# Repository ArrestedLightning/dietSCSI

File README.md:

The dietSCSI is a SCSI disk emulator, designed to be low-cost while remaining highly functional.

Features
----------

* SMT-first design, optimized for modern low-cost assembly services
  * Target price of ~$10 each in small quantities from JLCPCB, fully assembled
  * This implies that the retail price for a fully-assembled board could be $20 with a 100% markup
* Can be [hand-assembled](https://youtu.be/Q2M2qIhKqx8) using only parts that are [readily available from DigiKey](https://www.digikey.com/short/dphdzd52) (Except for the STM32 microcontroller, but those aren't readily available anywhere at the moment)
* Integrated DB25 and 50-pin IDC connectors on one board.  A single PCB design covers multiple use cases, ideal for easy switching between multiple computers
  * This also means that you can use the dietSCSI itself as a DB-25 to 50-pin SCSI adapter in a pinch
* On-board termination (jumper-selectable)
* Design files for [3D printed cases](https://github.com/ArrestedLightning/dietSCSI/blob/main/Mechanical/README.md) are available in variants for both portable usage and 3.5" hard disk replacement
* 0.1" headers for external activity LEDs
* Can be powered via SCSI termination power or from an external source
* Designed to run firmware based on the open source [BlueSCSI firmware](https://github.com/erichelgeson/BlueSCSI/)
* [Default firmware](https://github.com/ArrestedLightning/dietSCSI_firmware/) has both [USB image passthrough](https://youtu.be/Y3mzckQU518) and [USB firmware update support](https://youtu.be/odwWRFDpAHM) built in (see the [usage page](https://github.com/ArrestedLightning/dietSCSI/blob/main/docs/usage.md) for details).

Documentation
--------
* [Ordering assembled boards from JLCPCB](https://github.com/ArrestedLightning/dietSCSI/blob/main/docs/ordering_boards.md)
* [Hand assembly](https://github.com/ArrestedLightning/dietSCSI/blob/main/docs/hand_assembly.md)
* [Finishing](https://github.com/ArrestedLightning/dietSCSI/blob/main/docs/finishing.md)
* [Usage](https://github.com/ArrestedLightning/dietSCSI/blob/main/docs/usage.md)
* [Test Results](https://github.com/ArrestedLightning/dietSCSI/blob/main/docs/testresults.md)

Acknowledgments
--------

* The [ARDSCSuino-stm32](https://github.com/ztto/ArdSCSino-stm32) project for the original implementation of STM32-to-SCSI hardware and firmware
* [This TI document](https://www.ti.com/lit/an/slla035/slla035.pdf) on SCSI termination
* The [BlueSCSI project](https://github.com/erichelgeson/BlueSCSI/) for their work on the firmware

BlueSCSI is a registered trademark.  This project is not affiliated with or endorsed by the BlueSCSI project.  Please do not contact the BlueSCSI people for support; use GitHub discussions or email me directly.

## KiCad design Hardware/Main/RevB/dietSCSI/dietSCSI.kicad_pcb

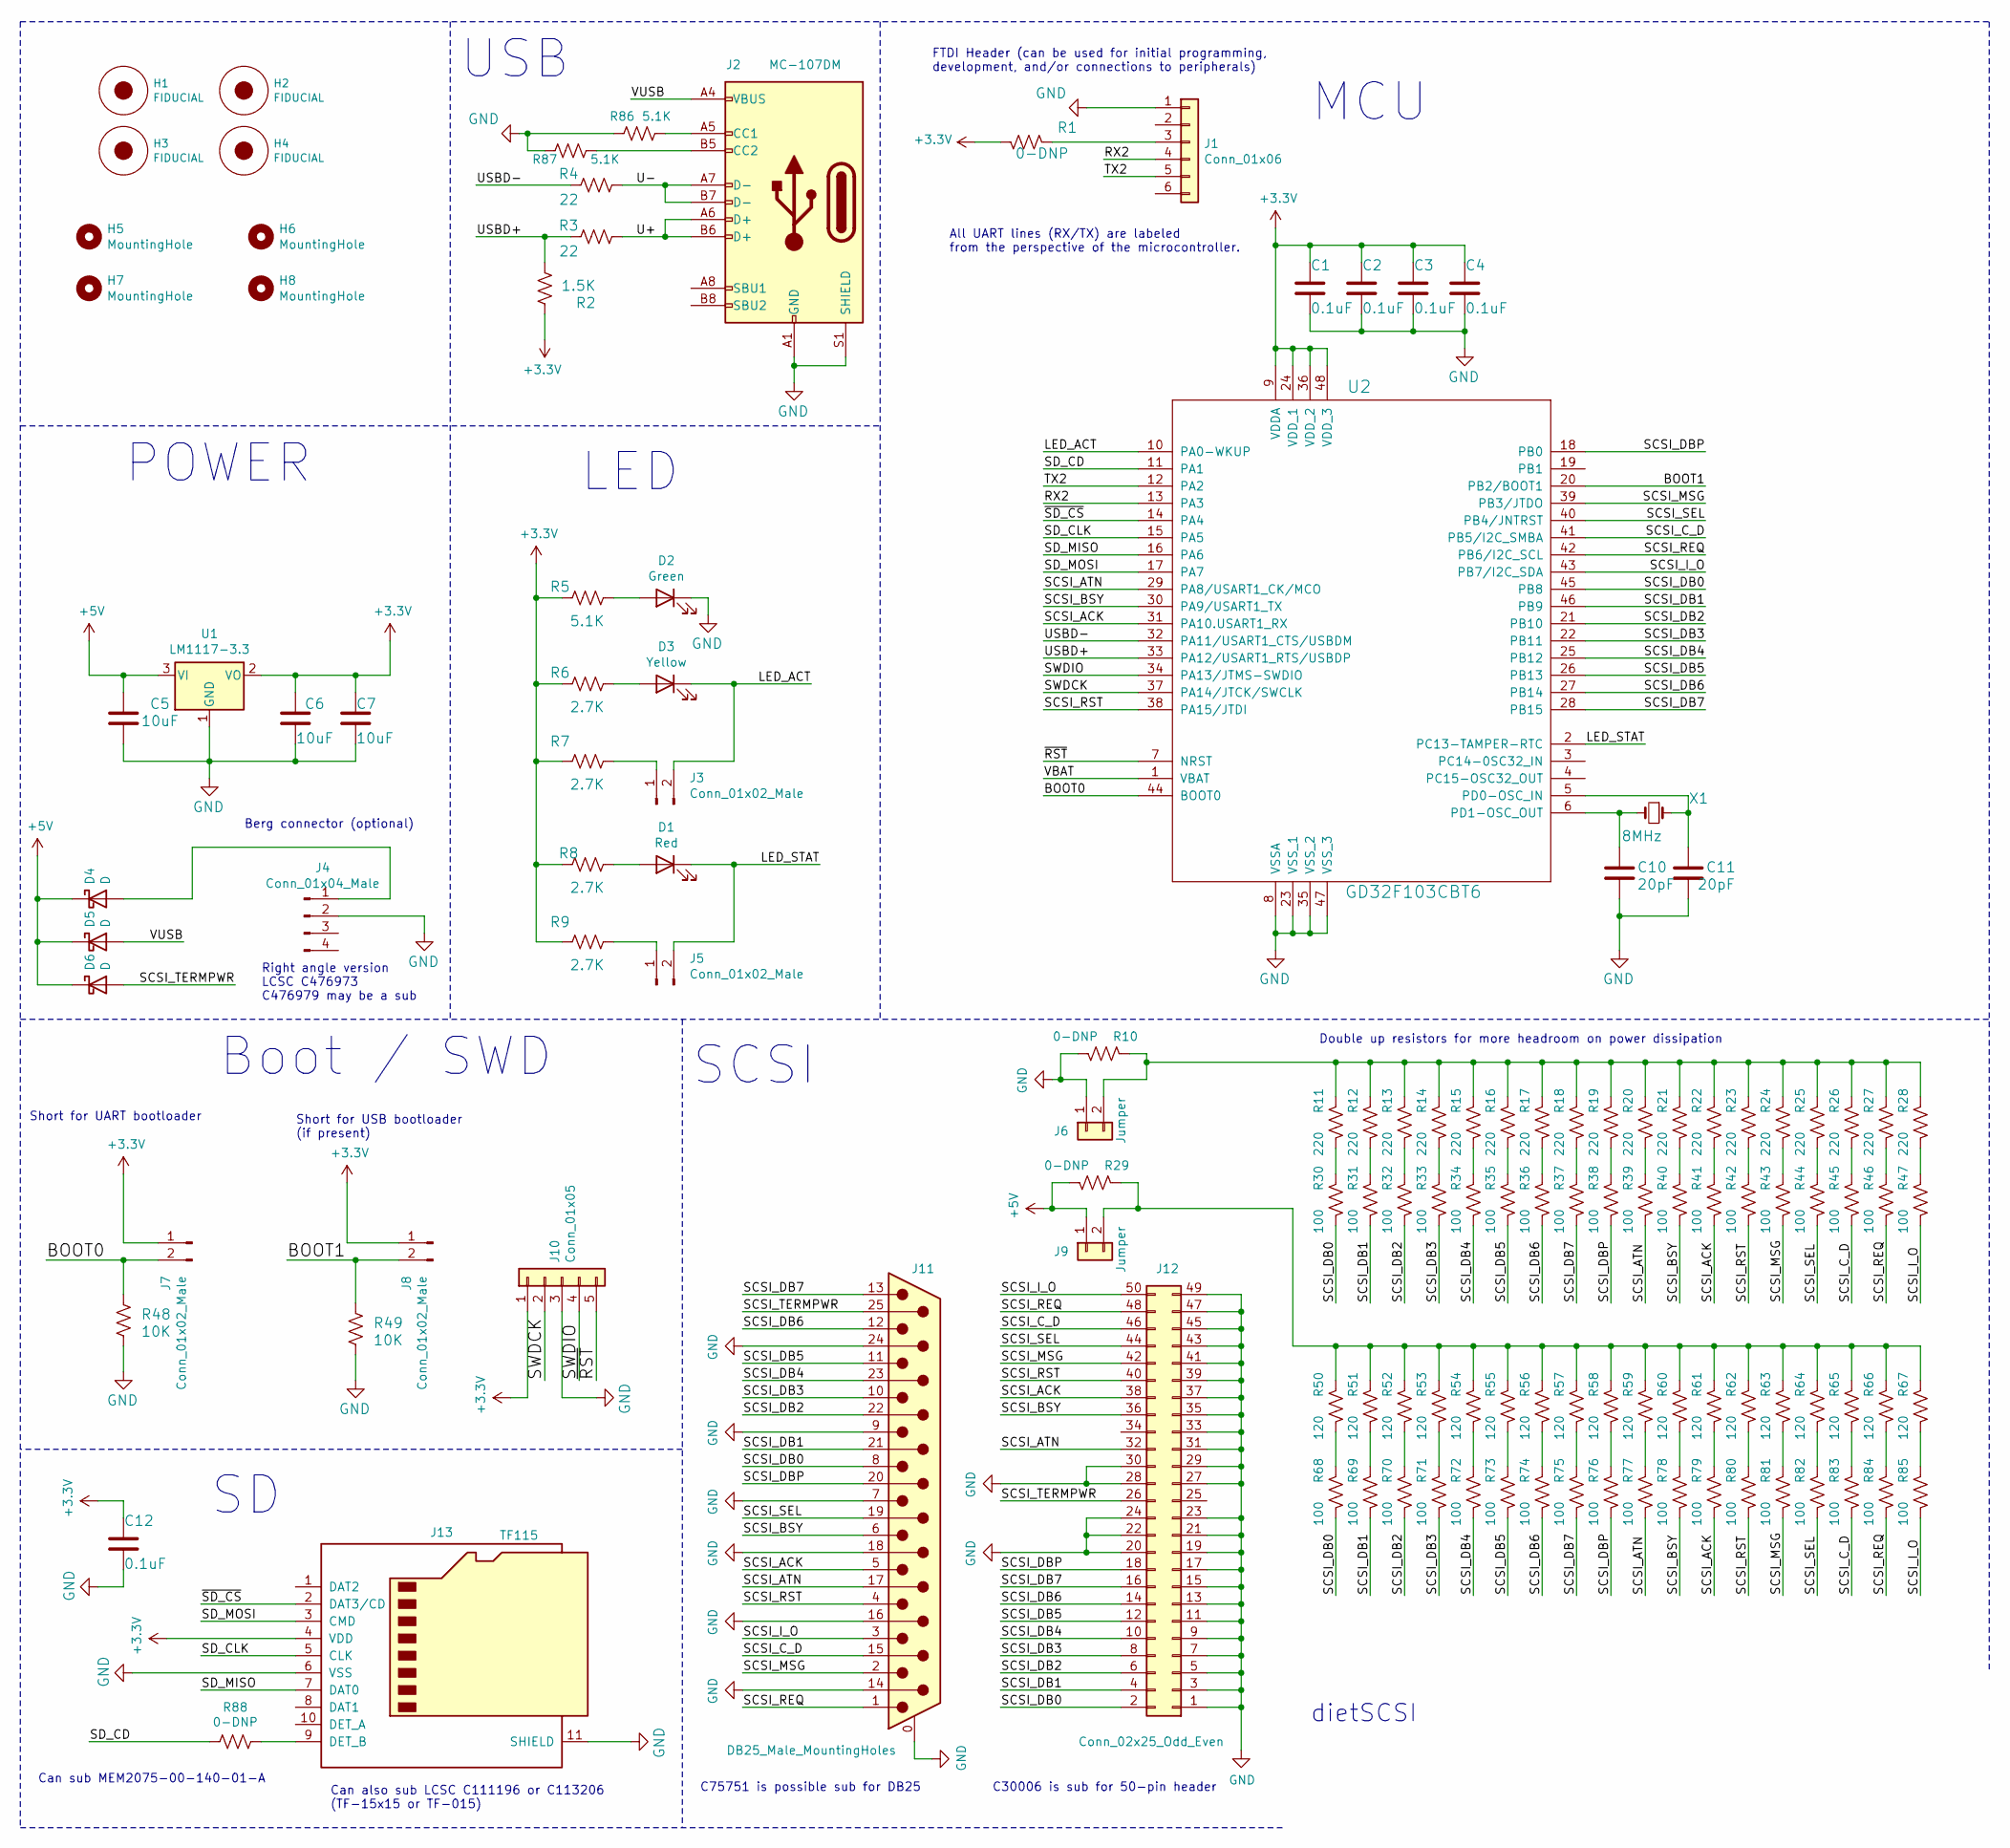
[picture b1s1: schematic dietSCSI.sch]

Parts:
C1, C2, C3, C4, C12: 0.1uF; C_0805_2012Metric_Pad1.18x1.45mm_HandSolder; JLCPCB C49678
C5, C6, C7: 10uF; C_1206_3216Metric_Pad1.33x1.80mm_HandSolder; JLCPCB C13585
C10, C11: 20pF; C_0805_2012Metric_Pad1.18x1.45mm_HandSolder; JLCPCB C1798
D1: Red; LED_0805_2012Metric_Pad1.15x1.40mm_HandSolder; JLCPCB C84256
D2: Green; LED_0805_2012Metric_Pad1.15x1.40mm_HandSolder; JLCPCB C2297
D3: Yellow; LED_0805_2012Metric_Pad1.15x1.40mm_HandSolder; JLCPCB C2296
D4, D5, D6: D; D_SOD-123; JLCPCB C8598
H1, H2, H3, H4: FIDUCIAL; Fiducial_1.5mm_Mask3mm
H5, H6, H7, H8: MountingHole; MountingHole_3mm_Pad
J1: Conn_01x06; PinHeader_1x06_P2.54mm_Vertical
J2: MC-107DM; USB_C_Receptacle_XKB_U262-16XN-4BVC11; JLCPCB C2874569
J3, J5, J7, J8: Conn_01x02_Male; PinHeader_1x02_P2.54mm_Vertical
J4: Conn_01x04_Male; BERG_4PIN; JLCPCB C210162
J6, J9: Jumper; PinHeader_1x02_P2.54mm_Vertical; JLCPCB C2894925
J10: Conn_01x05; PinHeader_1x05_P2.54mm_Vertical
J11: DB25_Male_MountingHoles; DSUB-25_Male_Horizontal_P2.77x2.84mm_EdgePinOffset7.70mm_Ho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; JLCPCB C190082
J12: Conn_02x25_Odd_Even; PinHeader_2x25_P2.54mm_Vertical_Shrouded; JLCPCB C601945
J13: TF115; TF-015_MEM2075_HYBRID; JLCPCB C266620
R1, R10, R29: 0-DNP; R_0805_2012Metric_Pad1.20x1.40mm_HandSolder
R2: 1.5K; R_0805_2012Metric_Pad1.20x1.40mm_HandSolder; JLCPCB C4310
R3, R4: 22; R_0805_2012Metric_Pad1.20x1.40mm_HandSolder; JLCPCB C17561
R5, R86, R87: 5.1K; R_0805_2012Metric_Pad1.20x1.40mm_HandSolder; JLCPCB C27834
R6, R7, R8, R9: 2.7K; R_0805_2012Metric_Pad1.20x1.40mm_HandSolder; JLCPCB C17530
R11, R12, R13, R14, R15, R16, R17, R18, R19, R20, R21, R22, R23, R24, R25, R26, R27, R28: 220; R_0805_2012Metric_Pad1.20x1.40mm_HandSolder; JLCPCB C17557
R30, R31, R32, R33, R34, R35, R36, R37, R38, R39, R40, R41, R42, R43, R44, R45, R46, R47, R68, R69, R70, R71, R72, R73, R74, R75, R76, R77, R78, R79, R80, R81, R82, R83, R84, R85: 100; R_0805_2012Metric_Pad1.20x1.40mm_HandSolder; JLCPCB C17408
R48, R49: 10K; R_0805_2012Metric_Pad1.20x1.40mm_HandSolder; JLCPCB C17414
R50, R51, R52, R53, R54, R55, R56, R57, R58, R59, R60, R61, R62, R63, R64, R65, R66, R67: 120; R_0805_2012Metric_Pad1.20x1.40mm_HandSolder; JLCPCB C17437
R88: 0-DNP; R_0402_1005Metric
U1: LM1117-3.3; SOT-223-3_TabPin2; JLCPCB C6186
U2: GD32F103CBT6; LQFP-48_7x7mm_P0.5mm; JLCPCB C77979
X1: 8MHz; Crystal_SMD_5032-2Pin_5.0x3.2mm; JLCPCB C115962

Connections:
+3V3: C1.1, C2.1, C3.1, C4.1, C6.1, C7.1, C12.1, J7.1, J8.1, J10.1, J13.4 (VDD), R1.1, R2.1, R5.1, R6.1, R7.1, R8.1, R9.1, U1.2 (VO), U2.9 (VDDA), U2.24 (VDD_1), U2.36 (VDD_2), U2.48 (VDD_3)
+5V: C5.1, D4.1 (K), D5.1 (K), D6.1 (K), J9.1, R29.2, U1.3 (VI)
/BOOT0: J7.2, R48.1, U2.44 (BOOT0)
/BOOT1: J8.2, R49.1, U2.20 (PB2/BOOT1)
/LED_ACT: D3.1 (K), J3.2, U2.10 (PA0-WKUP)
/LED_STAT: D1.1 (K), J5.2, U2.2 (PC13-TAMPER-RTC)
/RX2: J1.4, U2.13 (PA3)
/SCSI_ACK: J11.5, J12.38, R41.2, R79.2, U2.31 (PA10.USART1_RX)
/SCSI_ATN: J11.17, J12.32, R39.2, R77.2, U2.29 (PA8/USART1_CK/MCO)
/SCSI_BSY: J11.6, J12.36, R40.2, R78.2, U2.30 (PA9/USART1_TX)
/SCSI_C_D: J11.15, J12.46, R45.2, R83.2, U2.41 (PB5/I2C_SMBA)
/SCSI_DB0: J11.8, J12.2, R30.2, R68.2, U2.45 (PB8)
/SCSI_DB1: J11.21, J12.4, R31.2, R69.2, U2.46 (PB9)
/SCSI_DB2: J11.22, J12.6, R32.2, R70.2, U2.21 (PB10)
/SCSI_DB3: J11.10, J12.8, R33.2, R71.2, U2.22 (PB11)
/SCSI_DB4: J11.23, J12.10, R34.2, R72.2, U2.25 (PB12)
/SCSI_DB5: J11.11, J12.12, R35.2, R73.2, U2.26 (PB13)
/SCSI_DB6: J11.12, J12.14, R36.2, R74.2, U2.27 (PB14)
/SCSI_DB7: J11.13, J12.16, R37.2, R75.2, U2.28 (PB15)
/SCSI_DBP: J11.20, J12.18, R38.2, R76.2, U2.18 (PB0)
/SCSI_I_O: J11.3, J12.50, R47.2, R85.2, U2.43 (PB7/I2C_SDA)
/SCSI_MSG: J11.2, J12.42, R43.2, R81.2, U2.39 (PB3/JTDO)
/SCSI_REQ: J11.1, J12.48, R46.2, R84.2, U2.42 (PB6/I2C_SCL)
/SCSI_RST: J11.4, J12.40, R42.2, R80.2, U2.38 (PA15/JTDI)
/SCSI_SEL: J11.19, J12.44, R44.2, R82.2, U2.40 (PB4/JNTRST)
/SCSI_TERMPWR: D6.2 (A), J11.25, J12.26
/SD_CD: R88.2, U2.11 (PA1)
/SD_CLK: J13.5 (CLK), U2.15 (PA5)
/SD_MISO: J13.7 (DAT0), U2.16 (PA6)
/SD_MOSI: J13.3 (CMD), U2.17 (PA7)
/SWDCK: J10.2, U2.37 (PA14/JTCK/SWCLK)
/SWDIO: J10.4, U2.34 (PA13/JTMS-SWDIO)
/TX2: J1.5, U2.12 (PA2)
/U+: J2.A6 (D+), J2.B6 (D+), R3.2
/U-: J2.A7 (D-), J2.B7 (D-), R4.2
/USBD+: R2.2, R3.1, U2.33 (PA12/USART1_RTS/USBDP)
/USBD-: R4.1, U2.32 (PA11/USART1_CTS/USBDM)
/VBAT: U2.1 (VBAT)
/VUSB: D5.2 (A), J2.A4 (VBUS), J2.A9 (VBUS), J2.B4 (VBUS), J2.B9 (VBUS)
/~RST: J10.5, U2.7 (NRST)
/~SD_CS: J13.2 (DAT3/CD), U2.14 (PA4)
GND: C1.2, C2.2, C3.2, C4.2, C5.2, C6.2, C7.2, C10.2, C11.2, C12.2, D2.1 (K), J1.1, J2.A1 (GND), J2.A12 (GND), J2.B1 (GND), J2.B12 (GND), J2.S1 (SHIELD), J4.2, J6.1, J10.3, J11.0 (PAD), J11.7, J11.9, J11.14, J11.16, J11.18, J11.24, J12.1, J12.3, J12.5, J12.7, J12.9, J12.11, J12.13, J12.15, J12.17, J12.19, J12.20, J12.21, J12.22, J12.23, J12.24, J12.27, J12.28, J12.29, J12.30, J12.31, J12.33, J12.35, J12.37, J12.39, J12.41, J12.43, J12.45, J12.47, J12.49, J13.6 (VSS), J13.11 (SHIELD), R10.2, R48.2, R49.2, R86.2, R87.2, U1.1 (GND), U2.8 (VSSA), U2.23 (VSS_1), U2.35 (VSS_2), U2.47 (VSS_3)
unnamed: C10.1, U2.6 (PD1-OSC_OUT), X1.2
unnamed: C11.1, U2.5 (PD0-OSC_IN), X1.1
unnamed: D1.2 (A), R8.2
unnamed: D2.2 (A), R5.2
unnamed: D3.2 (A), R6.2
unnamed: D4.2 (A), J4.1
unnamed: J1.3, R1.2
unnamed: J2.A5 (CC1), R86.1
unnamed: J2.B5 (CC2), R87.1
unnamed: J3.1, R7.2
unnamed: J5.1, R9.2
unnamed: J6.2, R10.1, R11.1, R12.1, R13.1, R14.1, R15.1, R16.1, R17.1, R18.1, R19.1, R20.1, R21.1, R22.1, R23.1, R24.1, R25.1, R26.1, R27.1, R28.1
unnamed: J9.2, R29.1, R50.1, R51.1, R52.1, R53.1, R54.1, R55.1, R56.1, R57.1, R58.1, R59.1, R60.1, R61.1, R62.1, R63.1, R64.1, R65.1, R66.1, R67.1
unnamed: J13.9 (DET_B), R88.1
unnamed: R11.2, R30.1
unnamed: R12.2, R31.1
unnamed: R13.2, R32.1
unnamed: R14.2, R33.1
unnamed: R15.2, R34.1
unnamed: R16.2, R35.1
unnamed: R17.2, R36.1
unnamed: R18.2, R37.1
unnamed: R19.2, R38.1
unnamed: R20.2, R39.1
unnamed: R21.2, R40.1
unnamed: R22.2, R41.1
unnamed: R23.2, R42.1
unnamed: R24.2, R43.1
unnamed: R25.2, R44.1
unnamed: R26.2, R45.1
unnamed: R27.2, R46.1
unnamed: R28.2, R47.1
unnamed: R50.2, R68.1
unnamed: R51.2, R69.1
unnamed: R52.2, R70.1
unnamed: R53.2, R71.1
unnamed: R54.2, R72.1
unnamed: R55.2, R73.1
unnamed: R56.2, R74.1
unnamed: R57.2, R75.1
unnamed: R58.2, R76.1
unnamed: R59.2, R77.1
unnamed: R60.2, R78.1
unnamed: R61.2, R79.1
unnamed: R62.2, R80.1
unnamed: R63.2, R81.1
unnamed: R64.2, R82.1
unnamed: R65.2, R83.1
unnamed: R66.2, R84.1
unnamed: R67.2, R85.1

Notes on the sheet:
dietSCSI
Boot / SWD
MCU
LED
USB
Short for UART bootloader
Short for USB bootloader (if present)
FTDI Header (can be used for initial programming, development, and/or connections to peripherals)
All UART lines (RX/TX) are labeled from the perspective of the microcontroller.
SCSI
POWER
Berg connector (optional)
Right angle version LCSC C476973 C476979 may be a sub
Can also sub LCSC C111196 or C113206 (TF-15x15 or TF-015)
Double up resistors for more headroom on power dissipation
Can sub MEM2075-00-140-01-A
C75751 is possible sub for DB25
C30006 is sub for 50-pin header

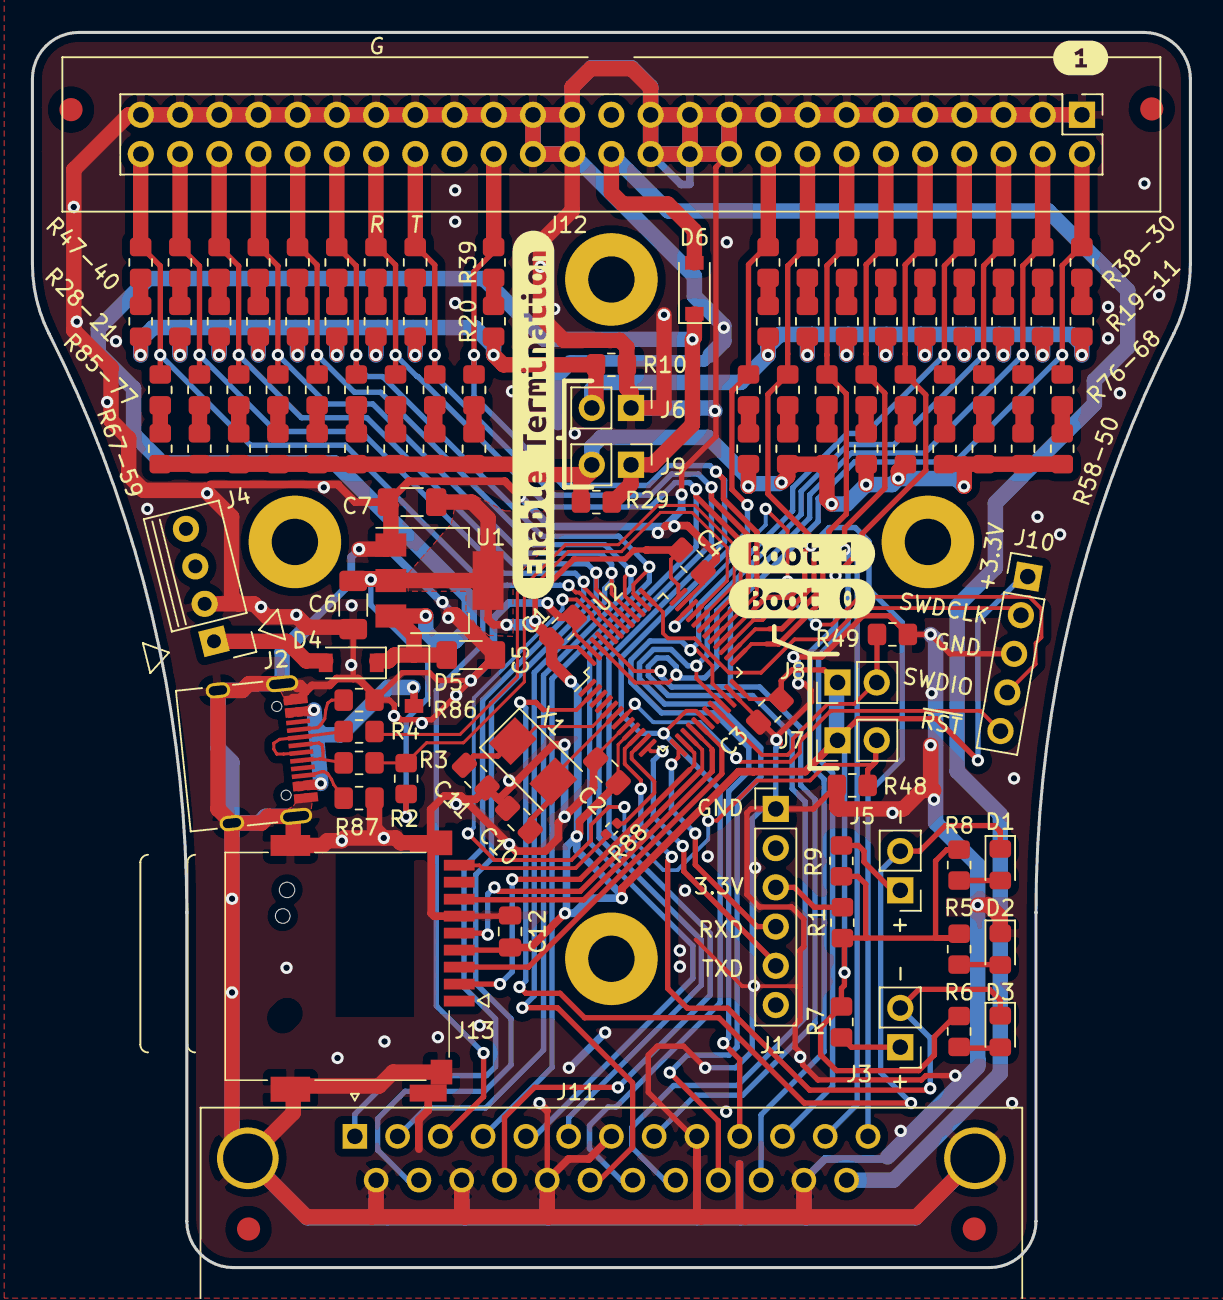
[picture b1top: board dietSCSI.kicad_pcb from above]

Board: 2 copper layers, 75.0 x 80.0 mm, 133 parts (1 on the bottom side), 91 nets.

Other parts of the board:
kibuzzard-61DE6C26, kibuzzard-61DE6C26#2, kibuzzard-62F7F5F5, kibuzzard-62F7F550, kibuzzard-62F7F576: G***; label

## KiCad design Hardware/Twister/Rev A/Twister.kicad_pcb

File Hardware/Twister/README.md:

SCSI Twister
==========
Some SCSI-based machines (e.g. the Mac LC series) expect their hard drive to be mounted such that the 50-pin connector ends up reversed compared to what the dietSCSI board expects.  The SCSI Twister is a simple board that I designed to flip the SCSI connection around to make it easier to install the dietSCSI board in those machines.  After designing it, I decided that I would prefer not to introduce any additional boards if at all possible, and instead modified the case design to allow the board to be installed upside down.  I have never built this board, and can therefore make no promises as to its functionality.  It is included here for the sake of completeness only.

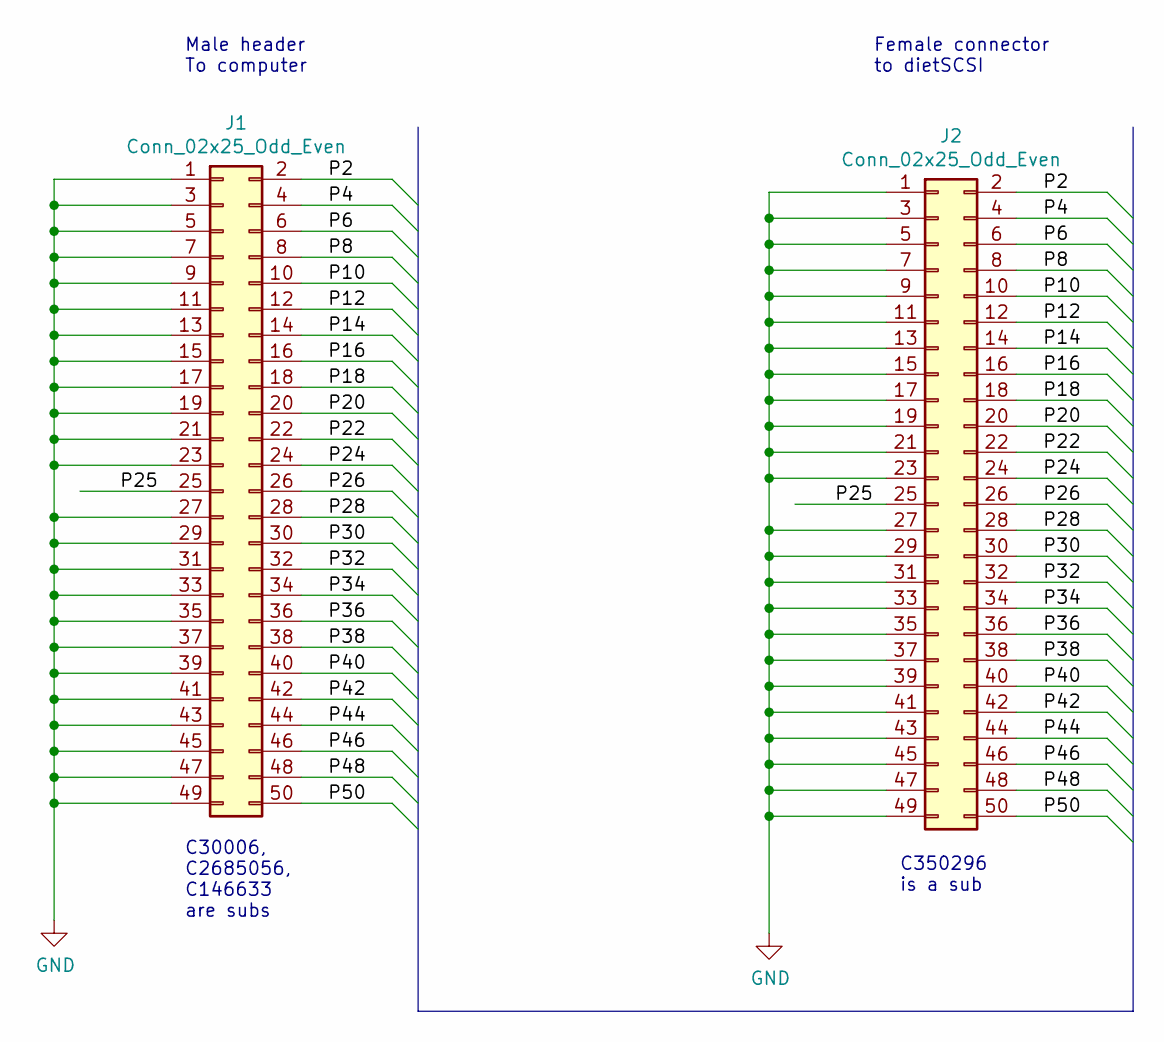
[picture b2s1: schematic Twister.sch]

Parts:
J1: Conn_02x25_Odd_Even; PinHeader_2x25_P2.54mm_Vertical_Shrouded; Digikey ED10530-ND
J2: Conn_02x25_Odd_Even; PinSocket_2x25_P2.54mm_Vertical; JLCPCB C40024

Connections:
/P2: J1.2, J2.2
/P4: J1.4, J2.4
/P6: J1.6, J2.6
/P8: J1.8, J2.8
/P10: J1.10, J2.10
/P12: J1.12, J2.12
/P14: J1.14, J2.14
/P16: J1.16, J2.16
/P18: J1.18, J2.18
/P20: J1.20, J2.20
/P22: J1.22, J2.22
/P24: J1.24, J2.24
/P25: J1.25, J2.25
/P26: J1.26, J2.26
/P28: J1.28, J2.28
/P30: J1.30, J2.30
/P32: J1.32, J2.32
/P34: J1.34, J2.34
/P36: J1.36, J2.36
/P38: J1.38, J2.38
/P40: J1.40, J2.40
/P42: J1.42, J2.42
/P44: J1.44, J2.44
/P46: J1.46, J2.46
/P48: J1.48, J2.48
/P50: J1.50, J2.50
GND: J1.1, J1.3, J1.5, J1.7, J1.9, J1.11, J1.13, J1.15, J1.17, J1.19, J1.21, J1.23, J1.27, J1.29, J1.31, J1.33, J1.35, J1.37, J1.39, J1.41, J1.43, J1.45, J1.47, J1.49, J2.1, J2.3, J2.5, J2.7, J2.9, J2.11, J2.13, J2.15, J2.17, J2.19, J2.21, J2.23, J2.27, J2.29, J2.31, J2.33, J2.35, J2.37, J2.39, J2.41, J2.43, J2.45, J2.47, J2.49

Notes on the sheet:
Male header To computer
Female connector to dietSCSI
C30006, C2685056, C146633 are subs
C350296 is a sub

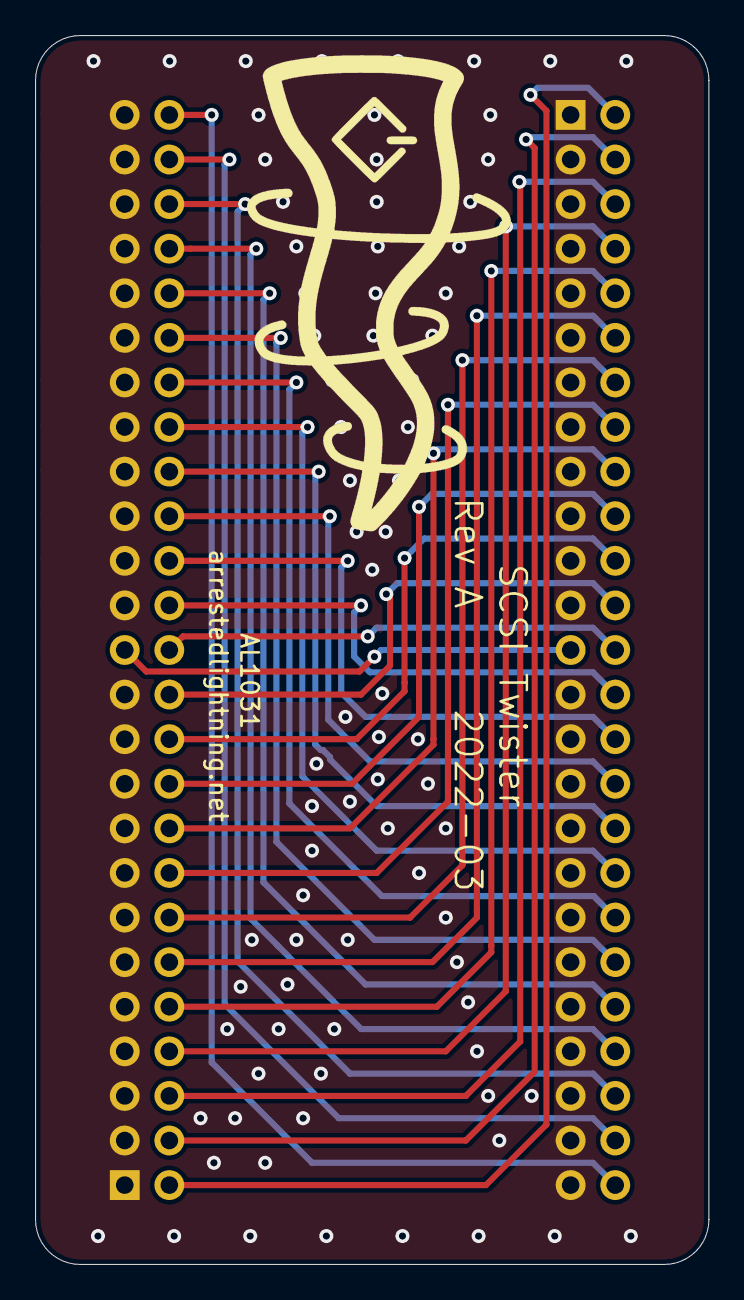
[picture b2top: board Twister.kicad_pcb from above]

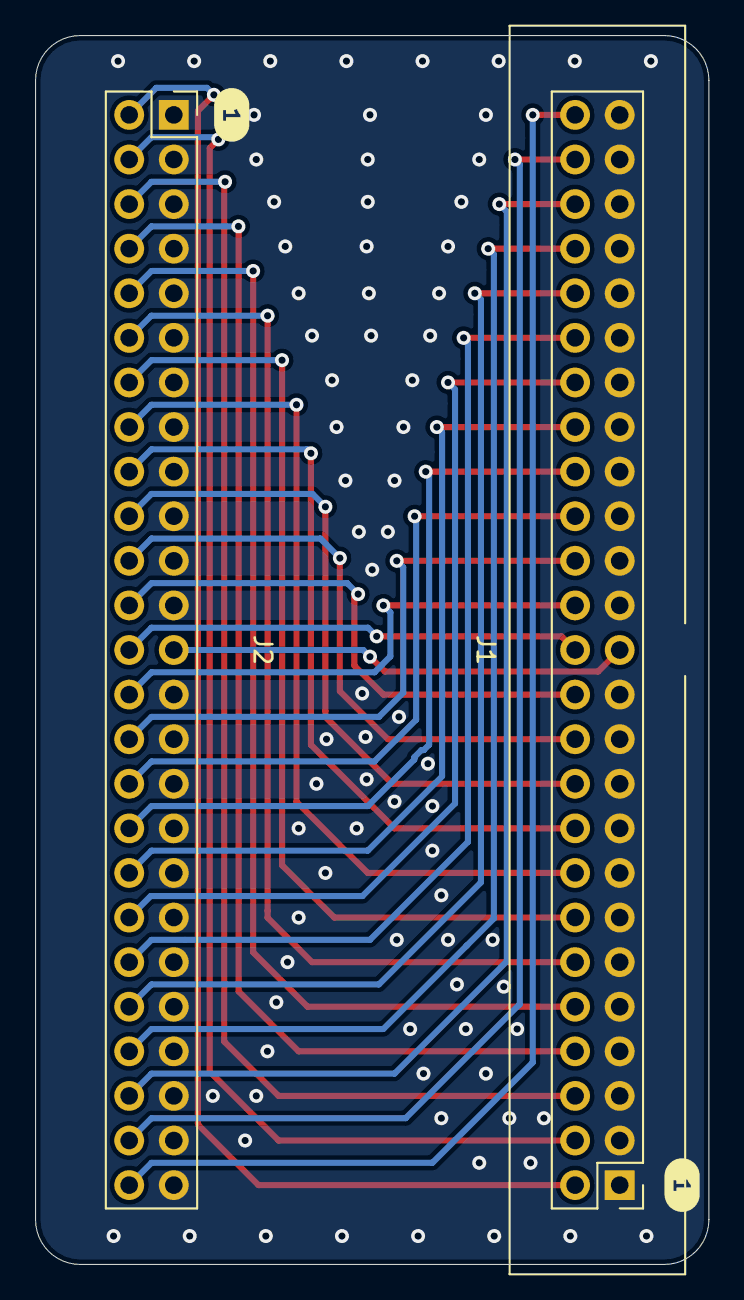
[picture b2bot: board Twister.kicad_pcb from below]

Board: 2 copper layers, 38.4 x 70.0 mm, 4 parts (4 on the bottom side), 27 nets.

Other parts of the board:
kibuzzard-622EC2D7, kibuzzard-622EC2D7#2: G***; label

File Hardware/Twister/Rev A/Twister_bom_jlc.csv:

"Comment","Designator","Footprint","LCSC Part #"
"Conn_02x25_Odd_Even","J1","PinHeader_2x25_P2.54mm_Vertical_Shrouded","C601945"
"Conn_02x25_Odd_Even","J2","PinSocket_2x25_P2.54mm_Vertical","C40024"

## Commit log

2022-09-10 A few small documentation updates
